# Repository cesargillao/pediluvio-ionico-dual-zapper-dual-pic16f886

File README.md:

# Dual Pediluvio Iónico con Zapper (Básico y Pro) (PIC16F886)

## Se proporciona:
* Diagrama esquemático para emular el funcionamiento (Proteus)
* Diagrama esquemático y PCB (CadSoft Eagle)
* Software en C y ASM con su respectivo HEX (CCS Compiler)

### Si te gusta el proyecto, recomiendo dejar una estrella en el mismo o en mi perfil.
### Eso me inspira a seguir colaborando a la comunidad ❤.

# ⚠ Advertencia ⚠ 
### Este producto no ha sido probado más allá de una emulación mediante software y fue desarrollado con fines educativos. Por lo tanto, el uso que se le quiera dar a este proyecto es responsabilidad de quien lo implemente.

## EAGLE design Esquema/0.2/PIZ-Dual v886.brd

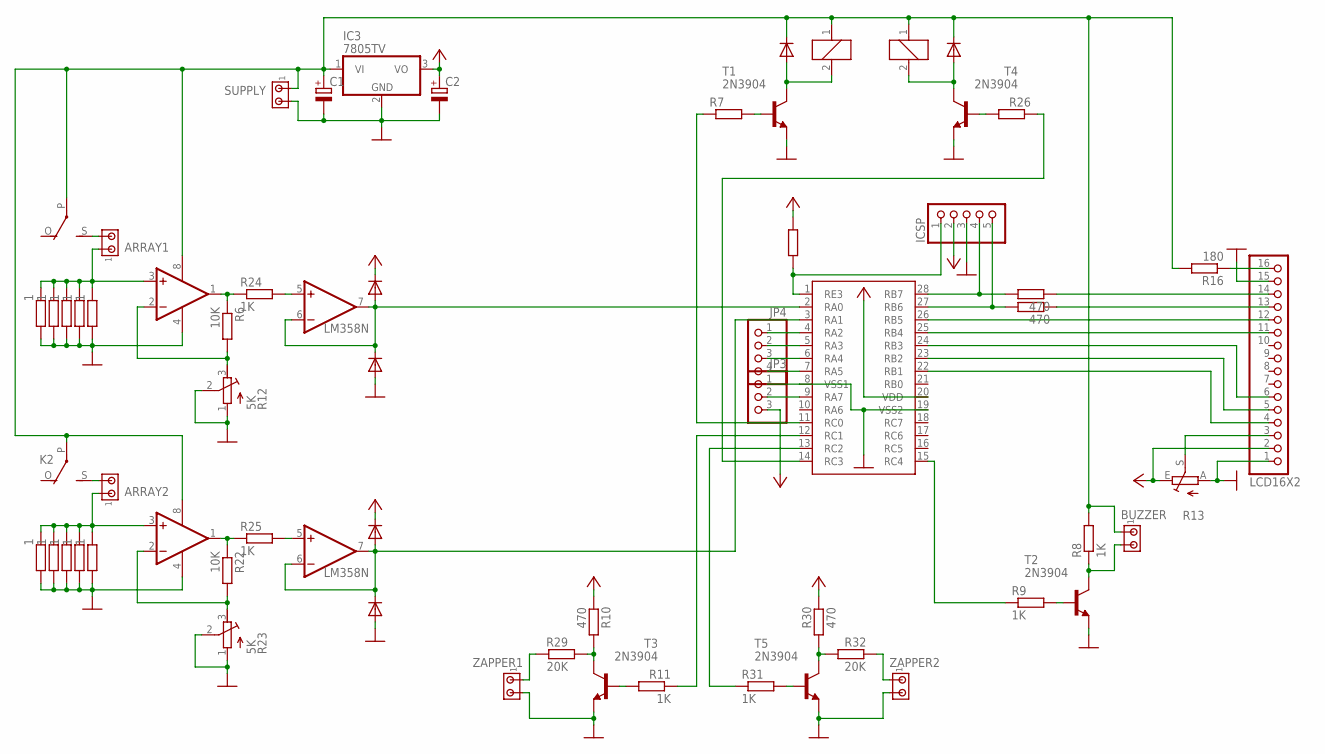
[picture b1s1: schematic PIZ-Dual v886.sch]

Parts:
ARRAY1, ARRAY2: MTA02-100; 10X02MTA
BUZZER: MTA02-100; 10X02MTA
C1, C2: CPOL-EUE2.5-7; E2,5-7
D1, D2, D3, D4, D5, D6: 1N4148DO35-7; DO35-7
IC2, IC4: LM358N; DIL08
IC3: 7805TV; TO220V
ICSP: PINHD-1X55X2MM; 1_05X2MM
JP3: PINHD-1X3; 1X03
JP4: PINHD-1X4; 1X04
K1, K2: G5L; G5LE
LCD16X2: PINHD-1X16; 1X16
R1, R2, R3, R4, R5, R17, R18, R19, R20, R21: 1; 0204/7
R6, R22, R33: 10K; 0204/7
R7, R26: R-EU_0204/7; 0204/7
R8, R9, R11, R24, R25, R31: 1K; 0204/7
R10, R27, R28, R30: 470; 0204/7
R12, R23: 5K; RTRIM64W
R13: TRIM_EU-CA6V; CA6V
R16: 180; 0309/10
R29, R32: 20K; 0204/7
SUPPLY: MTA02-100; 10X02MTA
T1, T2, T3, T4, T5: 2N3904; TO92
U$1: PIC16F88; SO28W
ZAPPER1, ZAPPER2: MTA02-100; 10X02MTA

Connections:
E: R11.1, U$1.12 (RC1)
GND: C1.-, C2.-, D2.A, D5.A, IC2.4 (V-), IC3.2 (GND), IC4.4 (V-), ICSP.3, JP3.1, LCD16X2.1, LCD16X2.15, R1.2, R2.2, R3.2, R4.2, R5.2, R12.1 (A), R12.2 (S), R13.A, R17.2, R18.2, R19.2, R20.2, R21.2, R23.1 (A), R23.2 (S), SUPPLY.2, T1.3 (E), T2.3 (E), T3.3 (E), T4.3 (E), T5.3 (E), U$1.8 (VSS1), U$1.19 (VSS2), ZAPPER1.2, ZAPPER2.2
unnamed: ARRAY1.1, IC2.3 (+IN), R1.1, R2.1, R3.1, R4.1, R5.1
unnamed: ARRAY1.2, K1.S
unnamed: IC2.1 (OUT), R6.1, R24.1
unnamed: IC2.2 (-IN), R6.2, R12.3 (E)
unnamed: BUZZER.2, R8.1, T2.1 (C)
unnamed: D1.A, D2.C, IC2.6 (-IN), IC2.7 (OUT), U$1.2 (RA0)
unnamed: D3.A, K1.2, T1.1 (C)
unnamed: R29.2, ZAPPER1.1
unnamed: R7.2, T1.2 (B)
unnamed: R9.2, T2.2 (B)
unnamed: R11.2, T3.2 (B)
unnamed: R9.1, U$1.15 (RC4)
unnamed: LCD16X2.4, U$1.22 (RB1)
unnamed: R7.1, U$1.11 (RC0)
unnamed: LCD16X2.14, R27.1
unnamed: LCD16X2.13, R28.1
unnamed: LCD16X2.12, U$1.26 (RB5)
unnamed: LCD16X2.11, U$1.25 (RB4)
unnamed: ARRAY2.1, IC4.3 (+IN), R17.1, R18.1, R19.1, R20.1, R21.1
unnamed: LCD16X2.6, U$1.24 (RB3)
unnamed: LCD16X2.3, R13.S
unnamed: LCD16X2.5, U$1.23 (RB2)
unnamed: BUZZER.1, C1.+, D3.C, D6.C, IC2.8 (V+), IC3.1 (VI), IC4.8 (V+), K1.1, K1.P, K2.1, K2.P, R8.2, R16.2, SUPPLY.1
unnamed: LCD16X2.16, R16.1
unnamed: ICSP.5, R28.2, U$1.27 (RB6)
unnamed: ICSP.4, R27.2, U$1.28 (RB7)
unnamed: IC4.1 (OUT), R22.1, R25.1
unnamed: IC4.2 (-IN), R22.2, R23.3 (E)
unnamed: D4.A, D5.C, IC4.6 (-IN), IC4.7 (OUT), U$1.3 (RA1)
unnamed: ARRAY2.2, K2.S
unnamed: IC2.5 (+IN), R24.2
unnamed: IC4.5 (+IN), R25.2
unnamed: D6.A, K2.2, T4.1 (C)
unnamed: R26.2, T4.2 (B)
unnamed: R26.1, U$1.14 (RC3)
unnamed: R31.1, U$1.13 (RC2)
unnamed: R10.1, R29.1, T3.1 (C)
unnamed: R31.2, T5.2 (B)
unnamed: R32.2, ZAPPER2.1
unnamed: JP4.1, U$1.4 (RA2)
unnamed: R30.1, R32.1, T5.1 (C)
unnamed: ICSP.1, R33.2, U$1.1 (RE3)
unnamed: JP4.2, U$1.5 (RA3)
unnamed: JP4.3, U$1.6 (RA4)
unnamed: JP4.4, U$1.7 (RA5)
unnamed: JP3.2, U$1.9 (RA7)
VCC: C2.+, D1.C, D4.C, IC3.3 (VO), ICSP.2, JP3.3, LCD16X2.2, R10.2, R13.E, R30.2, R33.1, U$1.20 (VDD)

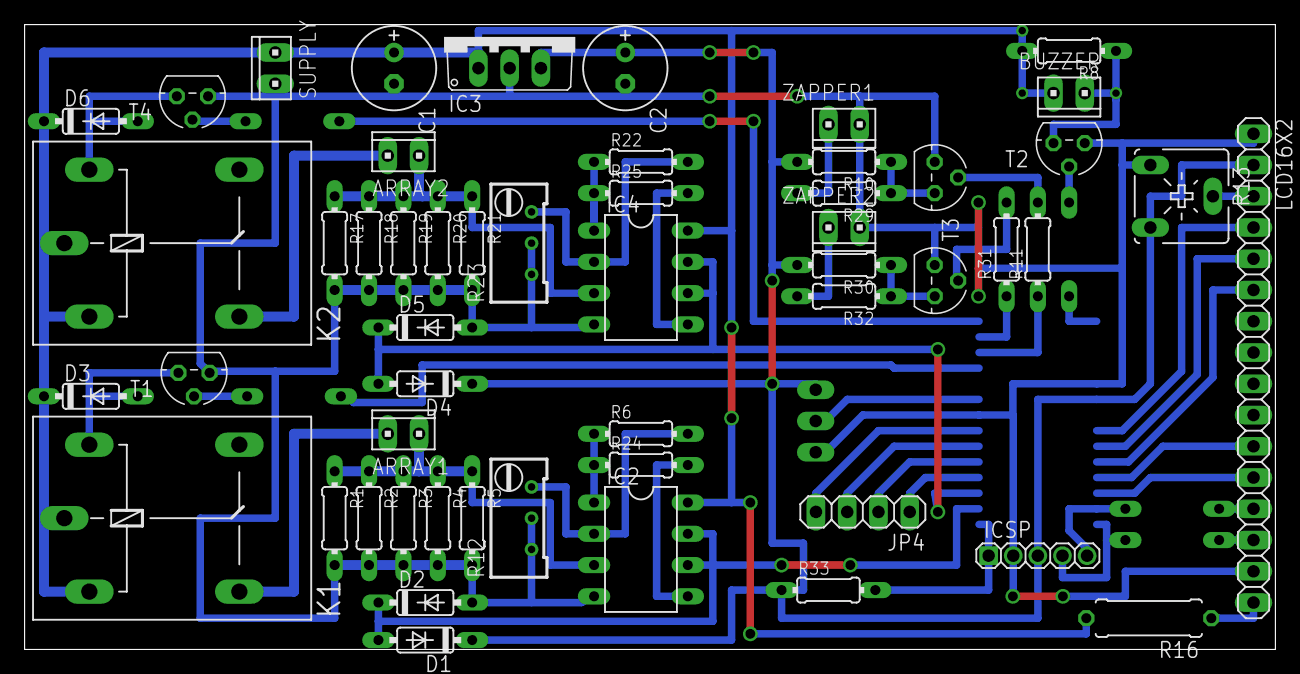
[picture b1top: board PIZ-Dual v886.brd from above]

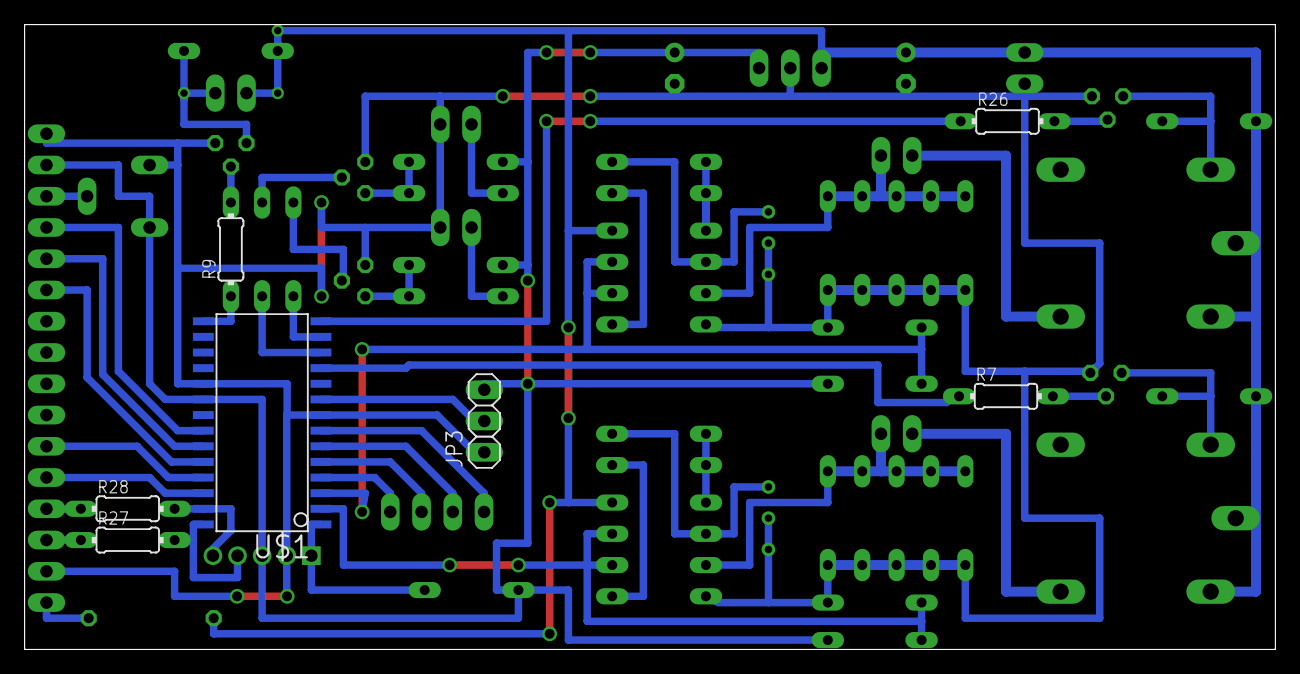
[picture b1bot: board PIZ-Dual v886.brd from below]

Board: 2 copper layers, 101.7 x 50.8 mm, 60 parts (7 on the bottom side), 49 nets.

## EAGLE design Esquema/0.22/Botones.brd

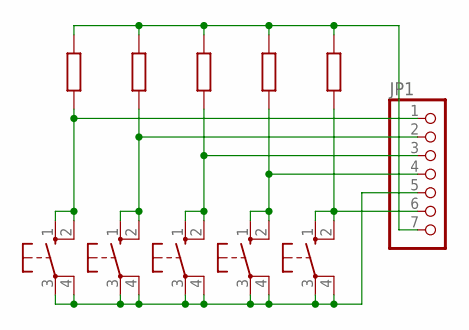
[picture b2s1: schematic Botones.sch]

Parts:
ABAJO: 10-XX; B3F-10XX
ARRIBA: 10-XX; B3F-10XX
DERECHA: 10-XX; B3F-10XX
IZQUIERDA: 10-XX; B3F-10XX
JP1: PINHD-1X7; 1X07
MENU: 10-XX; B3F-10XX
R14, R15, R34, R35, R36: 10K; 0204/7

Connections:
unnamed: DERECHA.1 (S), DERECHA.2 (S1), JP1.6, R36.2
unnamed: ARRIBA.1 (S), ARRIBA.2 (S1), JP1.1, R15.1
unnamed: ABAJO.1 (S), ABAJO.2 (S1), JP1.2, R14.1
unnamed: JP1.3, MENU.1 (S), MENU.2 (S1), R34.2
unnamed: IZQUIERDA.1 (S), IZQUIERDA.2 (S1), JP1.4, R35.2
unnamed: ABAJO.3, ABAJO.4 (P1), ARRIBA.3, ARRIBA.4 (P1), DERECHA.3, DERECHA.4 (P1), IZQUIERDA.3, IZQUIERDA.4 (P1), JP1.5, MENU.3, MENU.4 (P1)
unnamed: JP1.7, R14.2, R15.2, R34.1, R35.1, R36.1

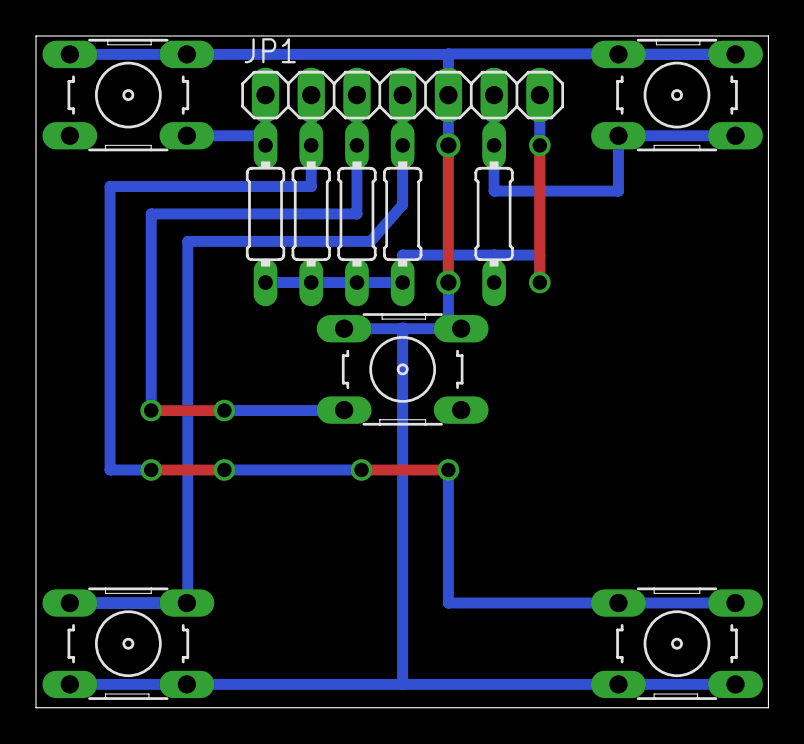
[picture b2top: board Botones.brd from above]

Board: 2 copper layers, 40.7 x 37.3 mm, 11 parts (0 on the bottom side), 7 nets.
